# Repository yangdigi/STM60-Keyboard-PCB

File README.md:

# STM60: an open source 60% keyboard
 
This repo is published under

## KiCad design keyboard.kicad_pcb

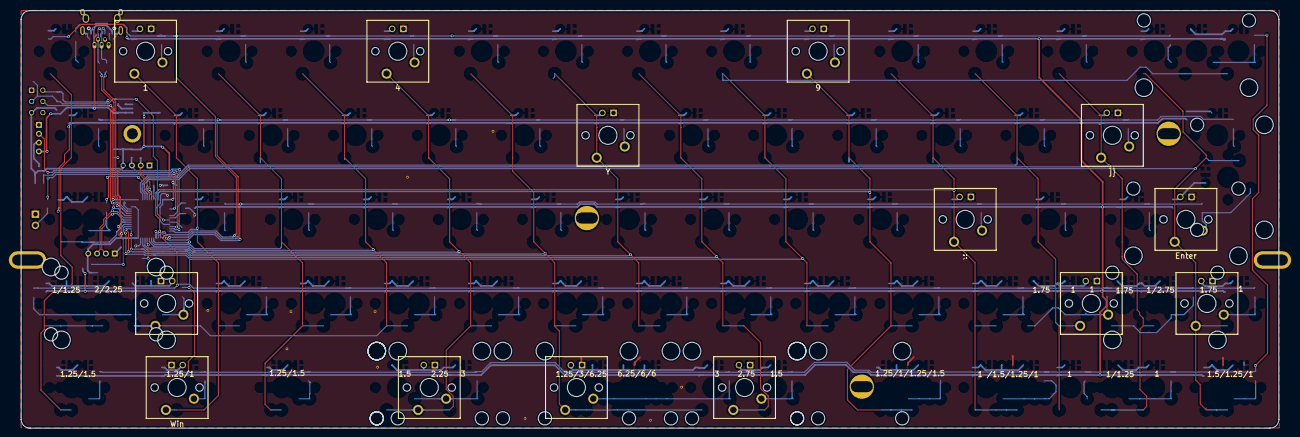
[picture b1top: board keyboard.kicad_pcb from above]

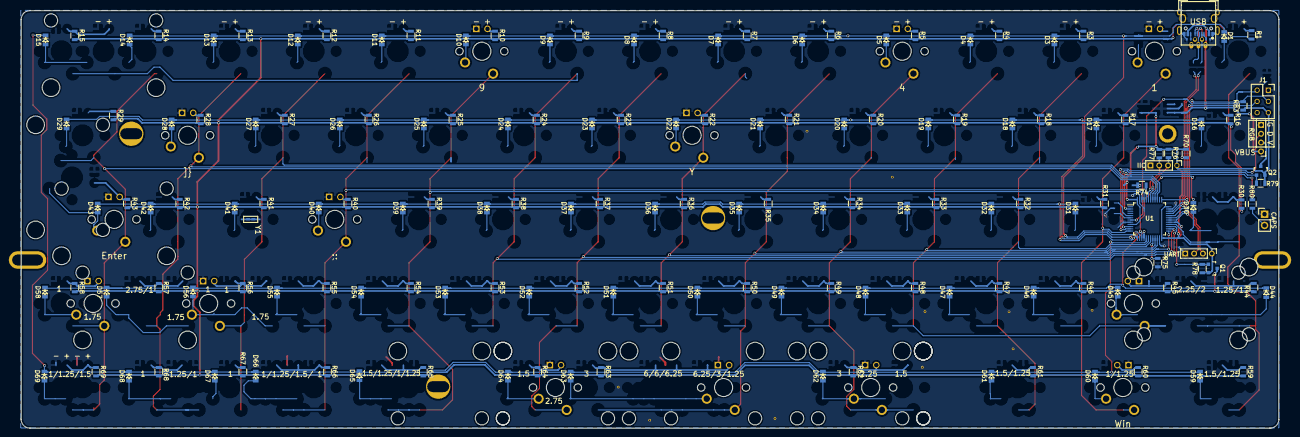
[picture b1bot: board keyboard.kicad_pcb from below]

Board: 2 copper layers, 285.0 x 94.6 mm, 188 parts (157 on the bottom side), 68 nets.

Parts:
D1, D3, D4, D5, D6, D7, D8, D9, D10, D11, D12, D13, D14, D15, D16, D17, D18, D19, D20, D21, D22, D23, D24, D25, D26, D27, D28, D29, D30, D31, D32, D33, D34, D35, D36, D37, D38, D39, D40, D41, D42, D43, D44, D45, D46, D47, D48, D49, D50, D51, D52, D53, D54, D55, D56, D57, D58, D59, D60, D61, D62, D63, D64, D65, D66, D67, D68, D69: 1n4148; D_0805
Hole0: Pad; PKRHSL
Hole0#2: VAL**; PKRHSL
Hole0#3, Hole0#4, Hole0#5: VAL**; PKRH
Hole0#6: VAL**; PKRHC
J1: SWD; 2x03_2.54_Small_hole
J2: RGB; Socket_Strip_Straight_1x04_Pitch2.00mm
J3: IIC; Socket_Strip_Straight_1x04_Pitch2.00mm
J4: UART; Socket_Strip_Straight_1x04_Pitch2.00mm
LED2: CAPS; Socket_Strip_Straight_1x02_Pitch2.54mm
Q1, Q2: MOS_P; SOT-23
R1, R3, R4, R5, R6, R7, R8, R9, R10, R11, R12, R13, R14, R15, R16, R17, R18, R19, R20, R21, R22, R23, R24, R25, R26, R27, R28, R29, R30, R31, R32, R33, R34, R35, R36, R37, R38, R39, R40, R41, R42, R43, R44, R45, R46, R47, R48, R49, R50, R51, R52, R53, R54, R55, R56, R57, R58, R59, R60, R61, R62, R63, R64, R65, R66, R67, R68, R69, R80: 300; R_0805
R70: 1K5; R_0805
R74, R75, R83: 10K; R_0805
R76, R77: 2K2; R_0805
R78, R79: 100K; R_0805
R81, R82: 5.1K; R_0402_NoSilk
S2: 1; MX1A_LED
S5: 4; MX1A_LED
S10: 9; MX1A_LED
S22: Y; MX1A_LED
S28: ]}; MX1A_LED
S40: ;:; MX1A_LED
S41: '; MX1A_LED
S43: Enter; MX1A_LED
S60: Win; MX1A_LED
S451: ISO\; MX1A_LED_NoText
S562: RShift; MX1A_LED_NoText
S581: Del; MX1A_LED_NoText
S622: Menu; MX1A_LED_NoText
S636: Space; MX1A_LED_NoText
S641: RWin; MX1A_LED_NoText
U1: STM32F103C8T6; LQFP-48_7x7mm_Pitch0.5mm
USB1: USB; DX_USB
USB2: USB_TYPE-C_16PIN; USB_TYPE-C_16PIN2
Val0, Val0#2, Val0#3, Val0#4, Val0#5, Val0#6, Val0#7, Val0#8, Val0#9, Val0#10: Pad; Via_0.6mm

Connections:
+3V3: J1.5, J3.1, J4.1, Q1.S, Q2.S, R70.1, R76.2, R77.2, R78.2, R79.2, R83.1, U1.9, U1.24, U1.36, U1.48
/.>2: S10.2, U1.46
//?2: S40.2, U1.45
/B2: S636.2, U1.22
/BOOT0: R74.1, U1.44
/BOOT1: R75.1, U1.20
/Backlight: Q1.D, R1.2, R3.2, R4.2, R5.2, R6.2, R7.2, R8.2, R9.2, R10.2, R11.2, R12.2, R13.2, R14.2, R15.2, R16.2, R17.2, R18.2, R19.2, R20.2, R21.2, R22.2, R23.2, R24.2, R25.2, R26.2, R27.2, R28.2, R29.2, R30.2, R31.2, R32.2, R33.2, R34.2, R35.2, R36.2, R37.2, R38.2, R39.2, R40.2, R41.2, R42.2, R43.2, R44.2, R45.2, R46.2, R47.2, R48.2, R49.2, R50.2, R51.2, R52.2, R53.2, R54.2, R55.2, R56.2, R57.2, R58.2, R59.2, R60.2, R61.2, R62.2, R63.2, R64.2, R65.2, R66.2, R67.2, R68.2, R69.2
/Backlight_C: Q1.G, R78.1, U1.29
/C2: S451.2, U1.19
/Caps_LED: R80.2, U1.2
/Col1: S2.2, S60.2, U1.12
/Col4: S5.2, S622.2, U1.21
/Col6: S22.2, U1.25
/Col7: S641.2, U1.26
/Col11: S562.2, U1.39
/Col12: S28.2, U1.40
/Col13: S43.2, S581.2, U1.41
/Del1: D58.1, S581.1
/Del3: R58.1, S581.3
/Enter1: D43.1, S43.1
/Enter3: R43.1, S43.3
/ISO\1: D45.1, S451.1
/ISO\3: R45.1, S451.3
/Menu1: D62.1, S622.1
/Menu3: R62.1, S622.3
/NRST: J1.3, R83.2, U1.7
/RGB_C: Q2.G, R79.1, U1.10
/RGB_Data: J2.3, U1.11
/RGB_VCC: J2.2, Q2.D
/RShift1: D56.1, S562.1
/RShift3: R56.1, S562.3
/RWin1: D64.1, S641.1
/RWin3: R64.1, S641.3
/RX: J4.2, U1.31
/Row0: D1.2, D3.2, D4.2, D5.2, D6.2, D7.2, D8.2, D9.2, D10.2, D11.2, D12.2, D13.2, D14.2, U1.13
/Row1: D16.2, D17.2, D18.2, D19.2, D20.2, D21.2, D22.2, D23.2, D24.2, D25.2, D26.2, D27.2, D28.2, D29.2, U1.14
/Row2: D30.2, D31.2, D32.2, D33.2, D34.2, D35.2, D36.2, D37.2, D38.2, D39.2, D40.2, D41.2, D42.2, D43.2, U1.15
/Row3: D44.2, D46.2, D47.2, D48.2, D49.2, D50.2, D51.2, D52.2, D53.2, D54.2, D55.2, D56.2, D57.2, D58.2, U1.16
/Row4: D15.2, D45.2, D59.2, D60.2, D61.2, D62.2, D63.2, D64.2, D65.2, D66.2, D67.2, D68.2, D69.2, U1.17
/SCL: J3.2, R76.1, U1.42
/SDA: J3.3, R77.1, U1.43
/SWCLK: J1.4, U1.37
/SWDIO: J1.2, U1.34
/Space1: D63.1, S636.1
/Space3: R63.1, S636.3
/TX: J4.3, U1.30
/USB_D+: USB1.3, USB2.6, USB2.8
/USB_D-: USB1.2, USB2.5, USB2.7
/Win1: D60.1, S60.1
/Win3: R60.1, S60.3
GNDPWR: J1.1, J2.4, J3.4, J4.4, LED2.1, R74.2, R75.2, R81.1, R82.1, S2.4, S5.4, S10.4, S22.4, S28.4, S40.4, S41.2, S43.4, S60.4, S451.4, S562.4, S581.4, S622.4, S636.4, S641.4, U1.8, U1.23, U1.35, U1.47, USB1.5, USB1.P$6, USB1.P$7, USB2.0, USB2.1, USB2.12, Val0.1, Val0#2.1, Val0#3.1, Val0#4.1, Val0#5.1, Val0#6.1, Val0#7.1, Val0#8.1, Val0#9.1, Val0#10.1
unnamed: D5.1, S5.1
unnamed: D10.1, S10.1
unnamed: D22.1, S22.1
unnamed: D28.1, S28.1
unnamed: D40.1, S40.1
unnamed: LED2.2, R80.1
unnamed: R5.1, S5.3
unnamed: R10.1, S10.3
unnamed: R22.1, S22.3
unnamed: R28.1, S28.3
unnamed: R40.1, S40.3
unnamed: R70.2, U1.33
unnamed: R81.2, USB2.4
unnamed: R82.2, USB2.10
unnamed: S41.1, U1.5
unnamed: S41.3, U1.6
VBUS: J2.1, USB1.1, USB2.2, USB2.11

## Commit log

2018-11-23 STM60_v1 by YANG

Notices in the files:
README.md:
License: CC BY-NC-SA 4.0
